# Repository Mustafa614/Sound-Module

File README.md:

# Sound-Module
This module contains all warning sounds of the automotive and supports can bus comminicate system

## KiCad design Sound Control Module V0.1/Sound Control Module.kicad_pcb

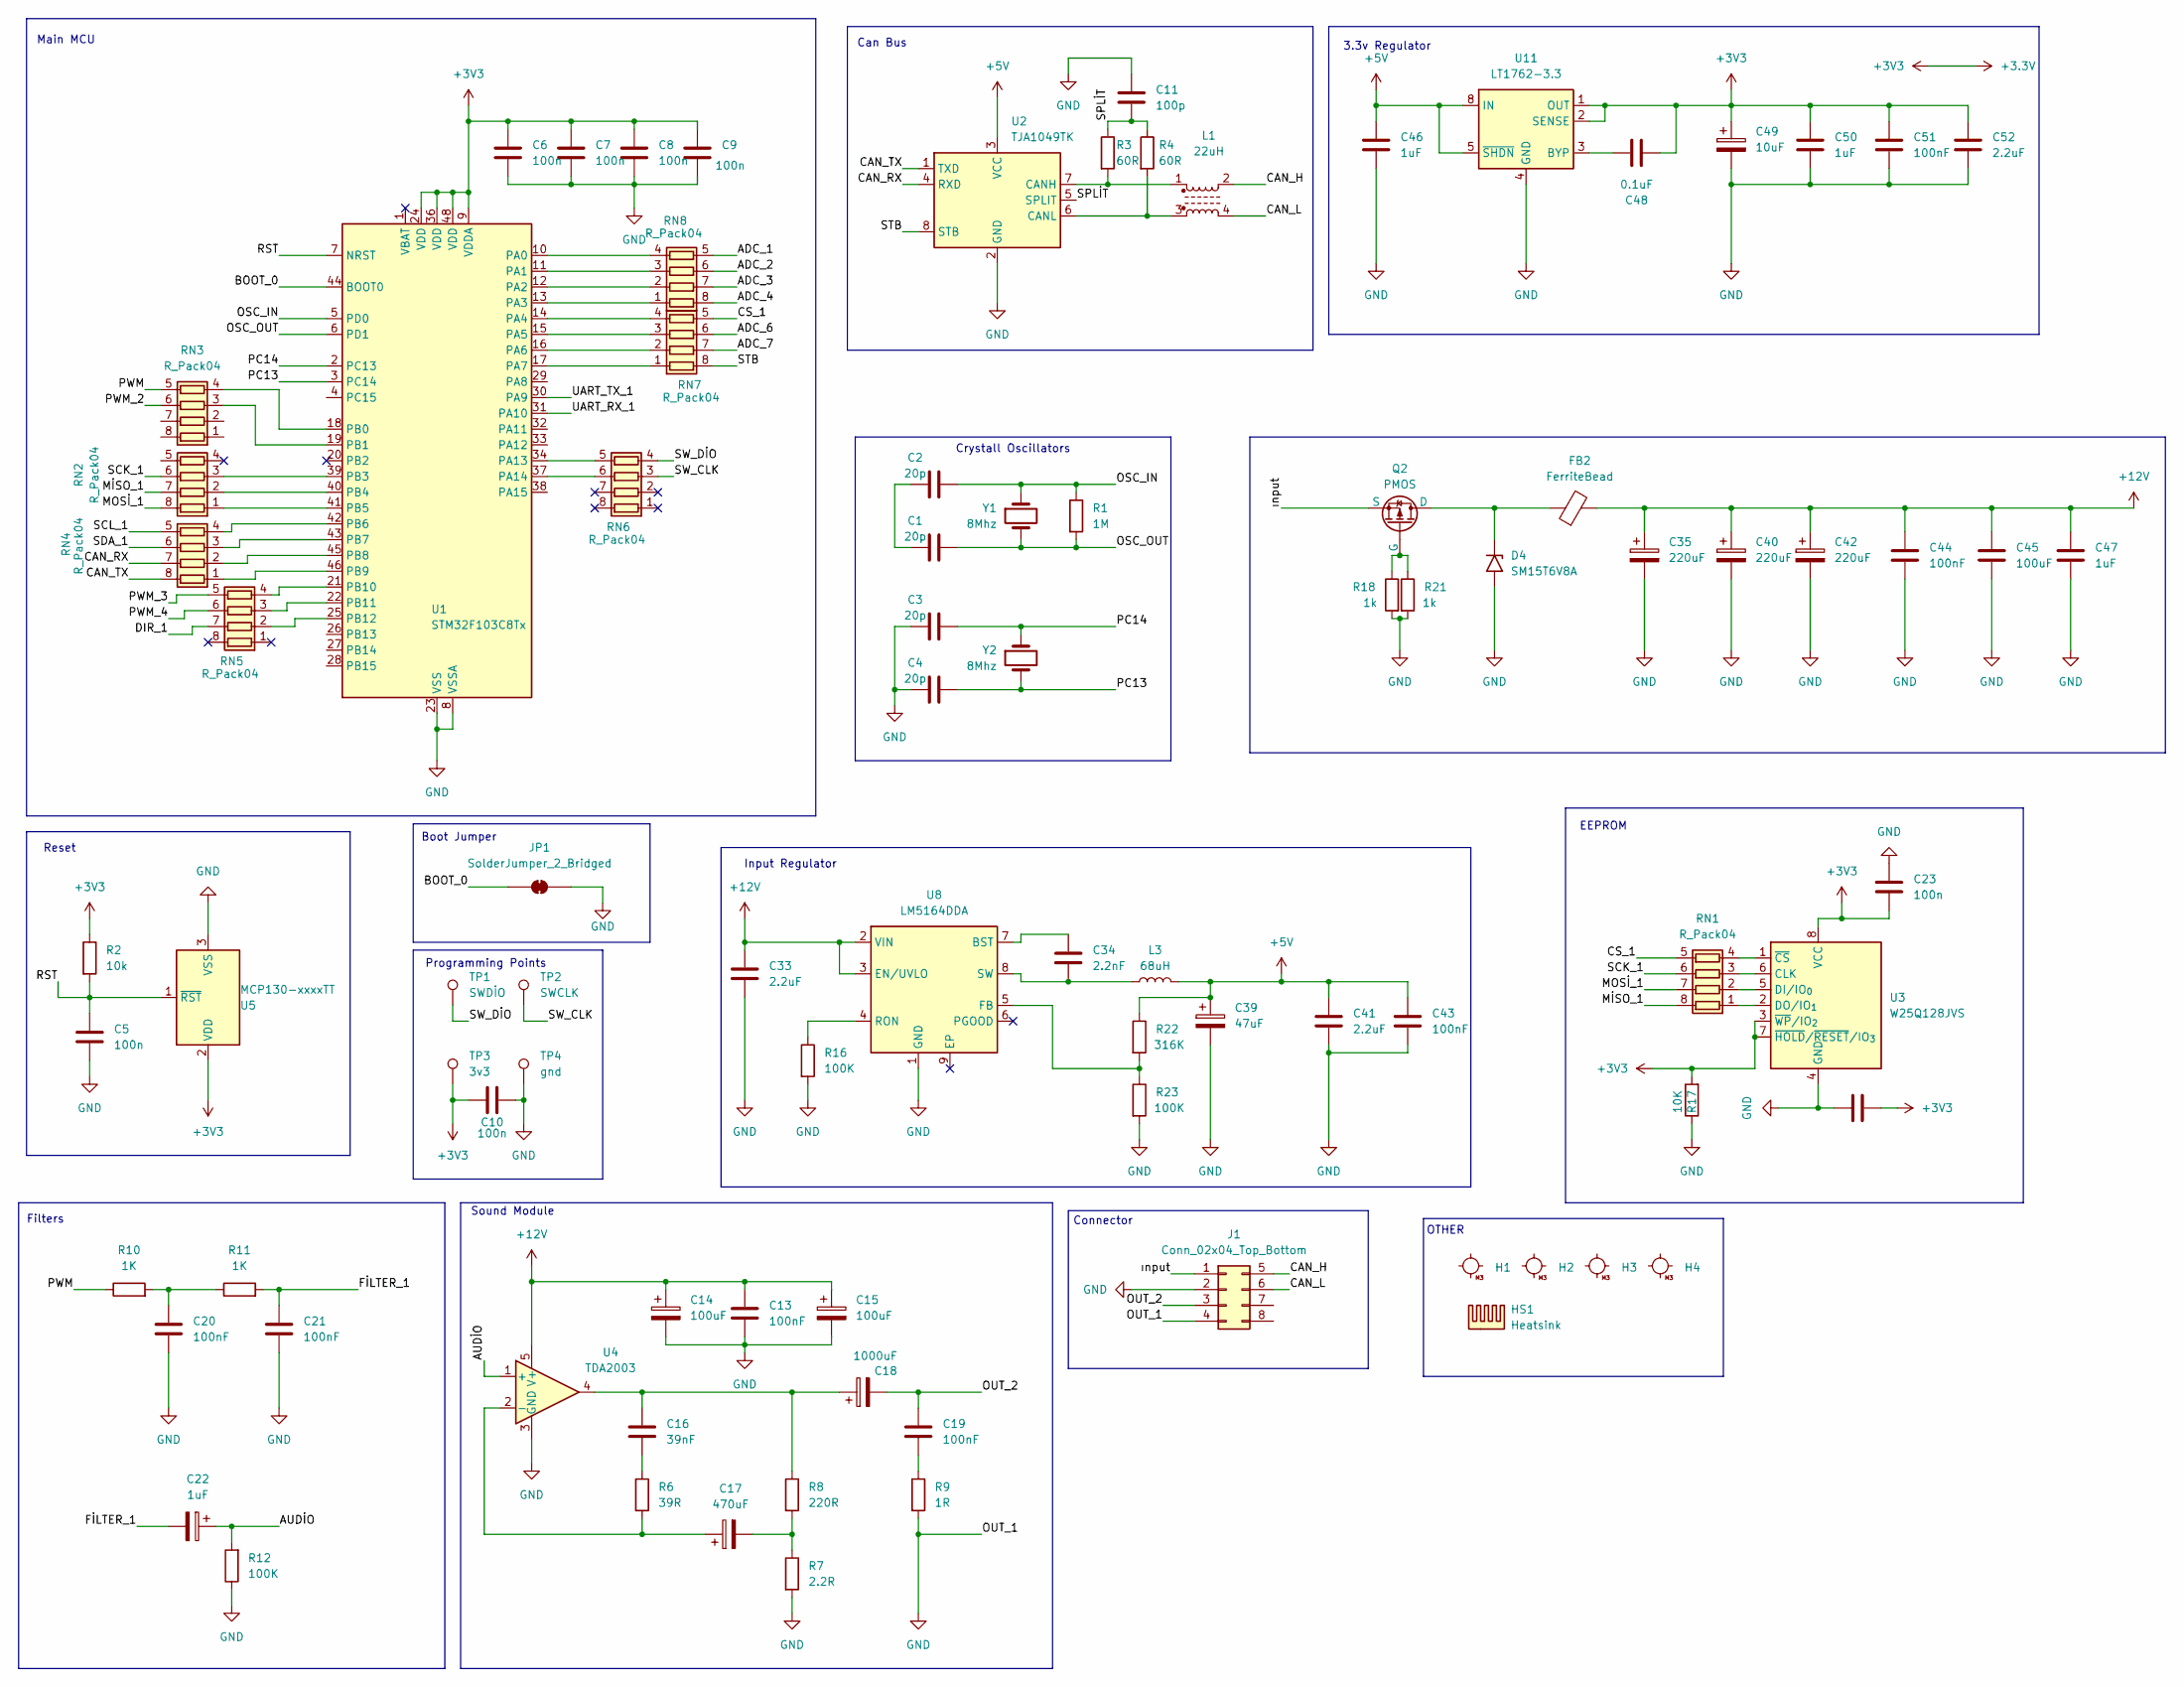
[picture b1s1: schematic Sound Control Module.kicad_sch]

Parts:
C1, C2, C3, C4: 20p; C_0603_1608Metric
C5: 100n; C_0402_1005Metric
C6, C7, C8, C9, C23, C24: 100n; C_0805_2012Metric
C10: 100n; C_0603_1608Metric
C11: 100p; C_0402_1005Metric
C13, C19, C20, C21: 100nF; C_1206_3216Metric
C14: 100uF; CP_EIA-3216-10_Kemet-I
C15: 100uF; CP_Elec_10x10
C16: 39nF; C_0805_2012Metric
C17: 470uF; CP_Elec_10x10
C18: 1000uF; CP_Elec_10x10
C22: 1uF; CP_Elec_5x3.9
C33, C41, C52: 2.2uF; C_0603_1608Metric
C34: 2.2nF; C_0603_1608Metric
C35, C40, C42: 220uF; CP_Radial_D14.0mm_P7.50mm
C39: 47uF; CP_Elec_6.3x4.9
C43, C44, C51: 100nF; C_0603_1608Metric
C45: 100uF; C_0603_1608Metric
C46, C47, C50: 1uF; C_0603_1608Metric
C48: 0.1uF; C_0603_1608Metric
C49: 10uF; CP_Elec_5x5.9
D4: SM15T6V8A; ST_D_SMC
FB2: FerriteBead; L_12x12mm_H8mm
H1, H2, H3, H4: MountingHole_M3
HS1: Heatsink; Heatsink_AAVID_Extruded_531002B00000G_34.9x12.7mm_H25.4mm
J1: Conn_02x04_Top_Bottom; IDC-Header_2x04_P2.54mm_Horizontal
JP1: SolderJumper_2_Bridged; SolderJumper-2_P1.3mm_Bridged2Bar_Pad1.0x1.5mm
L1: 22uH; L_CommonModeChoke_Coilank_ACM2012
L3: 68uH; L_12x12mm_H4.5mm
Q2: PMOS; TO-252-3_TabPin2
R1: 1M; R_0402_1005Metric
R2: 10k; R_0603_1608Metric
R3, R4: 60R; R_0603_1608Metric
R6: 39R; R_1206_3216Metric
R7: 2.2R; R_1206_3216Metric
R8: 220R; R_1206_3216Metric
R9: 1R; R_1206_3216Metric
R10, R11: 1K; R_0402_1005Metric
R12, R16: 100K; R_0402_1005Metric
R17: 10K; R_01005_0402Metric
R18, R21: 1k; R_0603_1608Metric
R22: 316K; R_0603_1608Metric
R23: 100K; R_0603_1608Metric
RN1, RN2, RN3, RN4, RN5, RN6, RN7, RN8: R_Pack04; R_Array_Concave_4x0603
TP1: SWDİO; TestPoint_Pad_1.0x1.0mm
TP2: SWCLK; TestPoint_Pad_1.0x1.0mm
TP3: 3v3; TestPoint_Pad_1.0x1.0mm
TP4: gnd; TestPoint_Pad_1.0x1.0mm
U1: STM32F103C8Tx; LQFP-48_7x7mm_P0.5mm
U2: TJA1049TK; SOIC-8_5.3x6.2mm_P1.27mm
U3: W25Q128JVS; SOIC-8_5.3x5.3mm_P1.27mm
U4: TDA2003; TO-220-5_P3.4x3.7mm_StaggerOdd_Lead3.8mm_Vertical
U5: MCP130-xxxxTT; SOT-23
U8: LM5164DDA; HSOP-8-1EP_3.9x4.9mm_P1.27mm_EP2.41x3.1mm_ThermalVias
U11: LT1762-3.3; MSOP-8_3x3mm_P0.65mm
Y1, Y2: 8Mhz; Crystal_HC49-U_Vertical

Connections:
+3.3V: C6.1, C7.1, C8.1, C9.1, C10.1, C23.1, C24.1, C48.1, C49.1, C50.1, C51.1, C52.1, R2.1, R17.2, TP3.1 (1_1), U1.9 (VDDA), U1.24 (VDD), U1.36 (VDD), U1.48 (VDD), U3.3 (~WP/IO_{2}), U3.7 (~HOLD/~RESET/IO_{3}), U3.8 (VCC), U5.2 (VDD), U11.1 (OUT), U11.2 (SENSE)
+5V: C39.1, C41.1, C43.1, C46.1, L3.2, R22.1, U2.3 (VCC), U11.5 (~SHDN), U11.8 (IN)
+12V: C13.1, C14.1, C15.1, C33.1, C35.1, C40.1, C42.1, C44.1, C45.1, C47.1, FB2.2, U4.5 (V+), U8.2 (VIN), U8.3 (EN/UVLO)
/ADC_1: RN8.5 (R4.2)
/ADC_2: RN8.6 (R3.2)
/ADC_3: RN8.7 (R2.2)
/ADC_4: RN8.8 (R1.2)
/ADC_6: RN7.6 (R3.2)
/ADC_7: RN7.7 (R2.2)
/AUDİO: C22.1, R12.2, U4.1 (+)
/BOOT_0: JP1.1 (A), U1.44 (BOOT0)
/CAN_H: J1.5, L1.2
/CAN_L: J1.6, L1.4
/CAN_RX: RN4.7 (R2.2), U2.4 (RXD)
/CAN_TX: RN4.8 (R1.2), U2.1 (TXD)
/CS_1: RN1.5 (R4.2), RN7.5 (R4.2)
/DIR_1: RN5.7 (R2.2)
/FİLTER_1: C21.1, C22.2, R11.2
/MOSİ_1: RN1.7 (R2.2), RN2.8 (R1.2)
/MİSO_1: RN1.8 (R1.2), RN2.7 (R2.2)
/OSC_IN: C2.2, R1.1, U1.5 (PD0), Y1.1
/OSC_OUT: C1.2, R1.2, U1.6 (PD1), Y1.2
/OUT_2: C18.2, C19.1, J1.3
/PC13: C4.2, U1.3 (PC14), Y2.2
/PC14: C3.2, U1.2 (PC13), Y2.1
/PWM: R10.1, RN3.5 (R4.2)
/PWM_2: RN3.6 (R3.2)
/PWM_3: RN5.5 (R4.2)
/PWM_4: RN5.6 (R3.2)
/RST: C5.1, R2.2, U1.7 (NRST), U5.1 (~RST)
/SCK_1: RN1.6 (R3.2), RN2.6 (R3.2)
/SCL_1: RN4.5 (R4.2)
/SDA_1: RN4.6 (R3.2)
/SPLİT: C11.2, R3.1, R4.1, U2.5 (SPLIT)
/STB: RN7.8 (R1.2), U2.8 (STB)
/SW_CLK: RN6.3 (R3.1), TP2.1 (1_1)
/SW_DİO: RN6.4 (R4.1), TP1.1 (1_1)
/UART_RX_1: U1.31 (PA10)
/UART_TX_1: U1.30 (PA9)
/ınput: J1.1, Q2.3 (S)
GND: C3.1, C4.1, C5.2, C6.2, C7.2, C8.2, C9.2, C10.2, C11.1, C13.2, C14.2, C15.2, C20.2, C21.2, C23.2, C24.2, C33.2, C35.2, C39.2, C40.2, C41.2, C42.2, C43.2, C44.2, C45.2, C46.2, C47.2, C49.2, C50.2, C51.2, C52.2, D4.2 (A2), J1.2, J1.4, JP1.2 (B), R7.2, R9.2, R12.1, R16.2, R17.1, R18.2, R21.2, R23.2, TP4.1 (1_1), U1.8 (VSSA), U1.23 (VSS), U1.35 (VSS), U1.47 (VSS), U2.2 (GND), U2.9 (GND), U3.4 (GND), U4.3 (GND), U5.3 (VSS), U8.1 (GND), U11.4 (GND)
unnamed: C1.1, C2.1
unnamed: C16.1, C18.1, R8.1, U4.4
unnamed: C16.2, R6.1
unnamed: C17.2, R7.1, R8.2
unnamed: C19.2, R9.1
unnamed: C20.1, R10.2, R11.1
unnamed: D4.1 (A1), FB2.1, Q2.1 (D)
unnamed: Q2.2 (G), R18.1, R21.1
unnamed: RN1.1 (R1.1), U3.2 (DO/IO_{1})
unnamed: RN1.2 (R2.1), U3.5 (DI/IO_{0})
unnamed: RN1.3 (R3.1), U3.6 (CLK)
unnamed: RN1.4 (R4.1), U3.1 (~CS)
unnamed: RN2.1 (R1.1), U1.41 (PB5)
unnamed: RN2.2 (R2.1), U1.40 (PB4)
unnamed: RN2.3 (R3.1), U1.39 (PB3)
unnamed: RN3.3 (R3.1), U1.19 (PB1)
unnamed: RN3.4 (R4.1), U1.18 (PB0)
unnamed: RN4.1 (R1.1), U1.46 (PB9)
unnamed: RN4.2 (R2.1), U1.45 (PB8)
unnamed: RN4.3 (R3.1), U1.43 (PB7)
unnamed: RN4.4 (R4.1), U1.42 (PB6)
unnamed: RN5.2 (R2.1), U1.25 (PB12)
unnamed: RN5.3 (R3.1), U1.22 (PB11)
unnamed: RN5.4 (R4.1), U1.21 (PB10)
unnamed: RN6.6 (R3.2), U1.37 (PA14)
unnamed: RN6.5 (R4.2), U1.34 (PA13)
unnamed: RN7.1 (R1.1), U1.17 (PA7)
unnamed: RN7.2 (R2.1), U1.16 (PA6)
unnamed: RN7.3 (R3.1), U1.15 (PA5)
unnamed: RN7.4 (R4.1), U1.14 (PA4)
unnamed: RN8.1 (R1.1), U1.13 (PA3)
unnamed: RN8.2 (R2.1), U1.12 (PA2)
unnamed: RN8.3 (R3.1), U1.11 (PA1)
unnamed: RN8.4 (R4.1), U1.10 (PA0)
unnamed: L1.1, R3.2, U2.7 (CANH)
unnamed: L1.3, R4.2, U2.6 (CANL)
unnamed: C17.1, R6.2, U4.2 (-)
unnamed: C34.1, U8.7 (BST)
unnamed: R22.2, R23.1, U8.5 (FB)
unnamed: R16.1, U8.4 (RON)
unnamed: C34.2, L3.1, U8.8 (SW)
unnamed: C48.2, U11.3 (BYP)

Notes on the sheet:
Reset
Can Bus
EEPROM
Sound Module
Connector
Crystall Oscillators
OTHER
3.3v Regulator
Programming Points
Filters
Main MCU
Input Regulator
Boot Jumper

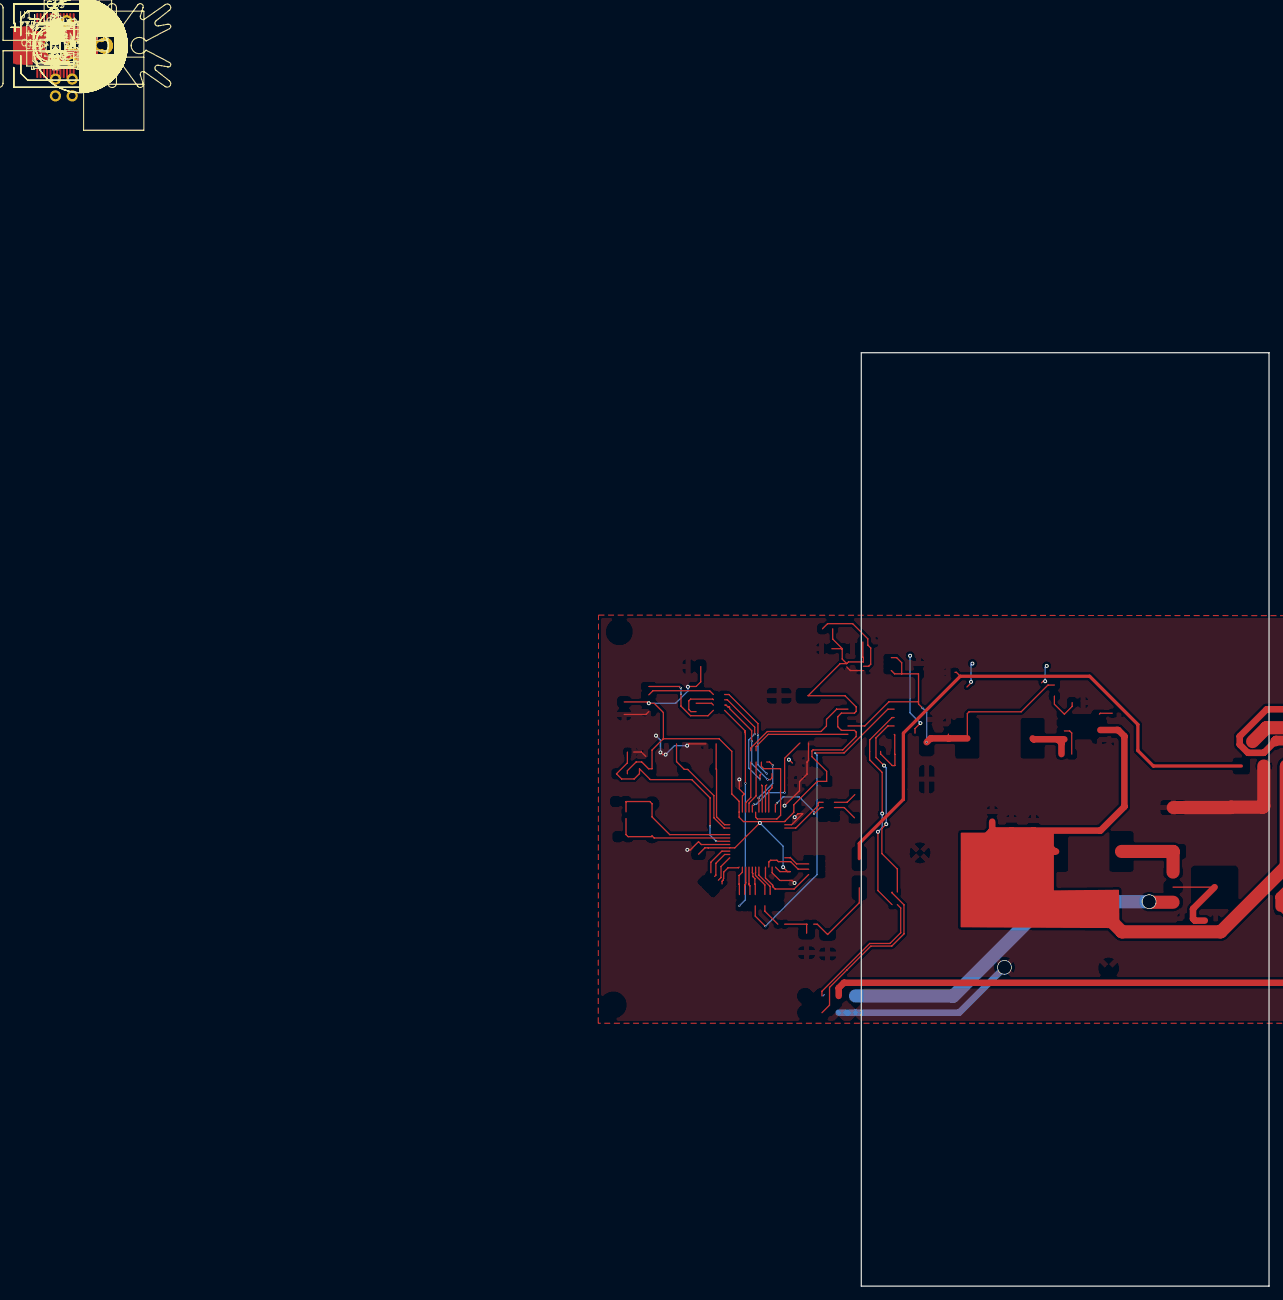
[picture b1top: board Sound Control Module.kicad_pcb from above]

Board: 2 copper layers, 90 parts (0 on the bottom side), 69 nets.
